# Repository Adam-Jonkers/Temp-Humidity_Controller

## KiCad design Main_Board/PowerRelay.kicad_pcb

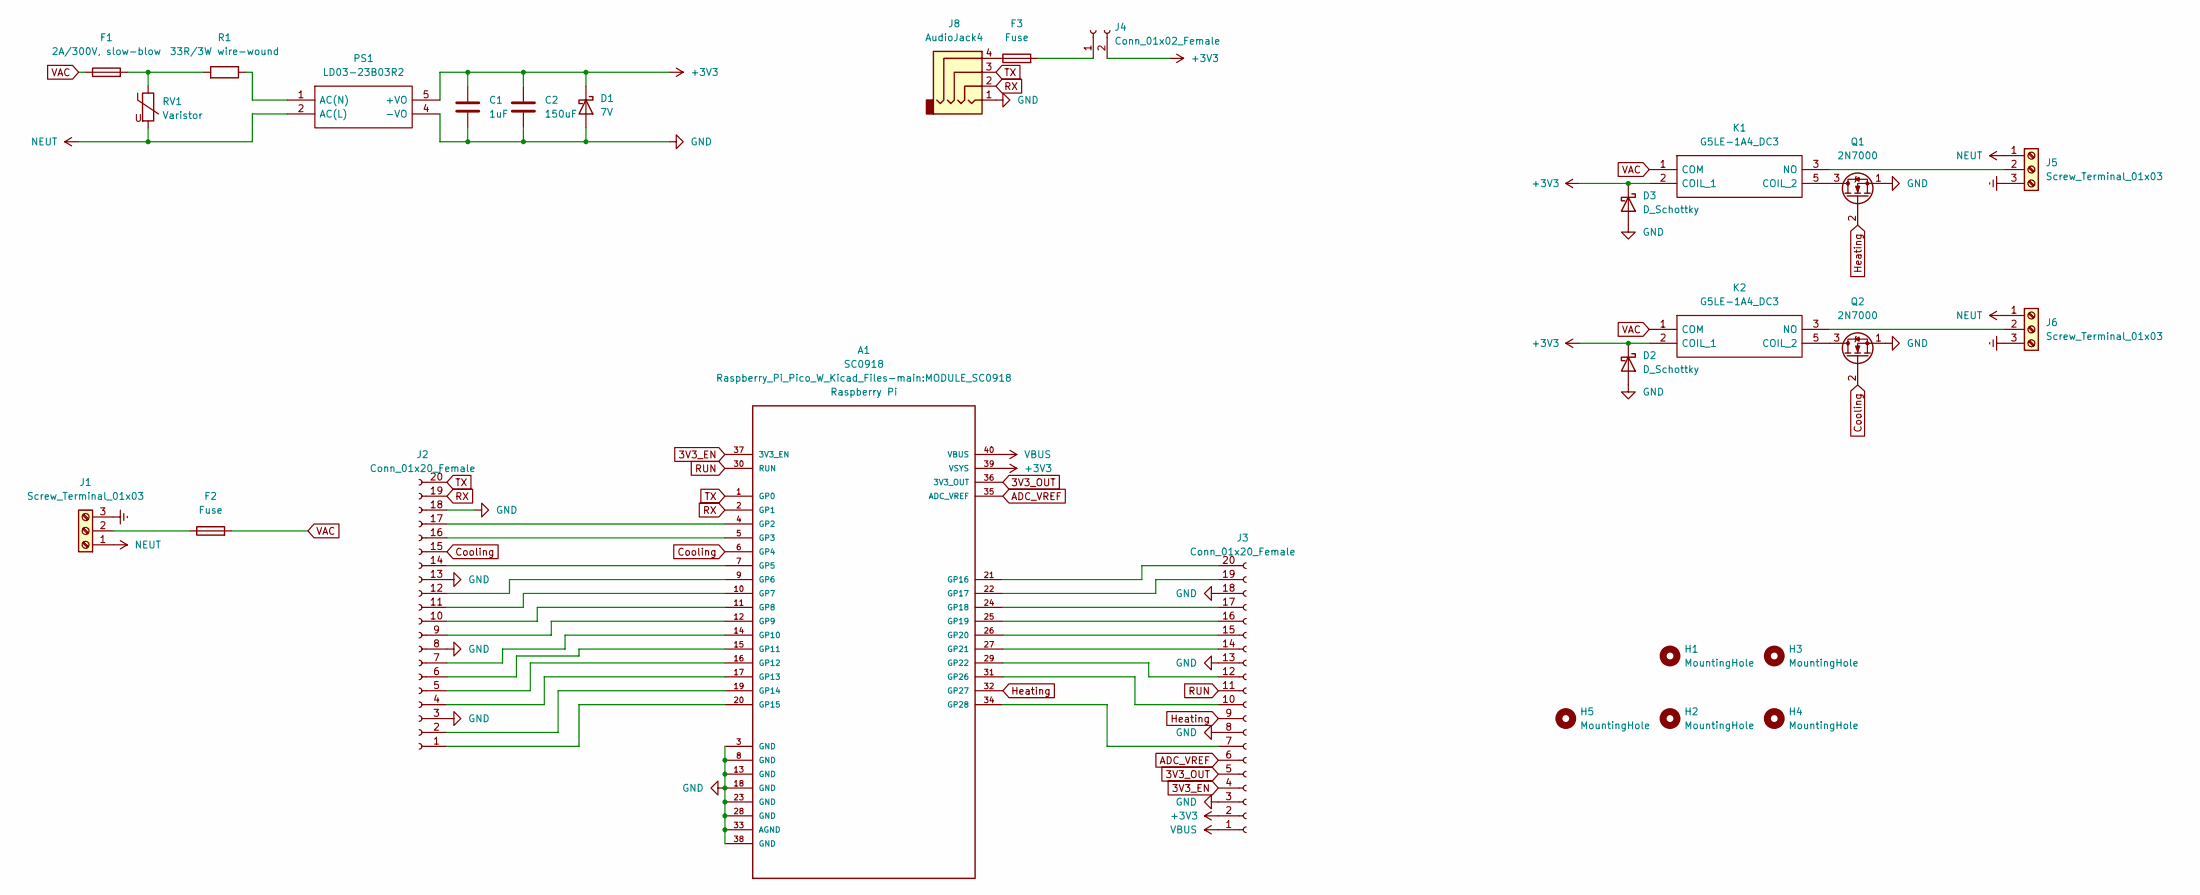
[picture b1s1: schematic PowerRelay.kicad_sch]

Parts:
A1: SC0918; MODULE_SC0918; PARTREV 1.6
C1: 1uF; C_Disc_D5.0mm_W2.5mm_P2.50mm
C2: 150uF; CP_Radial_D6.3mm_P2.50mm
D1: 7V; SA7.0A-E3_54
D2, D3: D_Schottky; DIOAD1300W80L670D310
F1: 2A/300V, slow-blow; 38312000000
F2: Fuse; 696105003002
F3: Fuse; 39105000000
H1, H2, H3, H4, H5: MountingHole; MountingHole_3mm
J1, J5, J6: Screw_Terminal_01x03; 1760520000
J2, J3: Conn_01x20_Female; PinHeader_1x20_P2.54mm_Vertical
J4: Conn_01x02_Female; PinHeader_1x02_P2.54mm_Vertical
J8: AudioJack4; 54-00174_JACK
K1, K2: G5LE-1A4_DC3; G5LE1A4DC3; Manufacturer_Part_Number G5LE-1A4 DC3; Mouser Part Number 653-G5LE-1A4DC3
PS1: LD03-23B03R2; LD0323B03R2; Manufacturer_Part_Number LD03-23B03R2
Q1, Q2: 2N7000; BS270
R1: 33R/3W wire-wound; AC03000003309JACCS
RV1: Varistor; B72214P2351K101

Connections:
3V3_EN: A1.37 (3V3_EN), J3.4
3V3_OUT: A1.36 (3V3_OUT), J3.5
+3V3: A1.39 (VSYS), C1.1, C2.1, D1.1 (K), D2.1 (K), D3.1 (K), J3.2, J4.2, K1.2 (COIL_1), K2.2 (COIL_1), PS1.5 (+VO)
ADC_VREF: A1.35 (ADC_VREF), J3.6
Cooling: A1.6 (GP4), J2.15, Q2.2 (G)
Earth: J1.3, J5.3, J6.3
GND: A1.3 (GND), A1.8 (GND), A1.13 (GND), A1.18 (GND), A1.23 (GND), A1.28 (GND), A1.33 (AGND), A1.38 (GND), C1.2, C2.2, D1.2 (A), D2.2 (A), D3.2 (A), J2.3, J2.8, J2.13, J2.18, J3.3, J3.8, J3.13, J3.18, J8.1, PS1.4 (-VO), Q1.1 (S), Q2.1 (S)
Heating: A1.32 (GP27), J3.9, Q1.2 (G)
NEUT: J1.1, J5.1, J6.1, PS1.2 (AC(L)), RV1.2
unnamed: A1.4 (GP2), J2.17
unnamed: A1.5 (GP3), J2.16
unnamed: A1.7 (GP5), J2.14
unnamed: A1.9 (GP6), J2.12
unnamed: A1.10 (GP7), J2.11
unnamed: A1.11 (GP8), J2.10
unnamed: A1.12 (GP9), J2.9
unnamed: A1.14 (GP10), J2.7
unnamed: A1.15 (GP11), J2.6
unnamed: A1.16 (GP12), J2.5
unnamed: A1.17 (GP13), J2.4
unnamed: A1.19 (GP14), J2.2
unnamed: A1.20 (GP15), J2.1
unnamed: A1.21 (GP16), J3.20
unnamed: A1.22 (GP17), J3.19
unnamed: A1.24 (GP18), J3.17
unnamed: A1.25 (GP19), J3.16
unnamed: A1.26 (GP20), J3.15
unnamed: A1.27 (GP21), J3.14
unnamed: A1.29 (GP22), J3.12
unnamed: A1.31 (GP26), J3.10
unnamed: A1.34 (GP28), J3.7
unnamed: F1.2, R1.2, RV1.1
unnamed: F3.1, J8.4
unnamed: F2.1, J1.2
unnamed: F3.2, J4.1
unnamed: J5.2, K1.3 (NO)
unnamed: J6.2, K2.3 (NO)
unnamed: K1.5 (COIL_2), Q1.3 (D)
unnamed: K2.5 (COIL_2), Q2.3 (D)
unnamed: PS1.1 (AC(N)), R1.1
RUN: A1.30 (RUN), J3.11
RX: A1.2 (GP1), J2.19, J8.2
TX: A1.1 (GP0), J2.20, J8.3
VAC: F1.1, F2.2, K1.1 (COM), K2.1 (COM)
VBUS: A1.40 (VBUS), J3.1

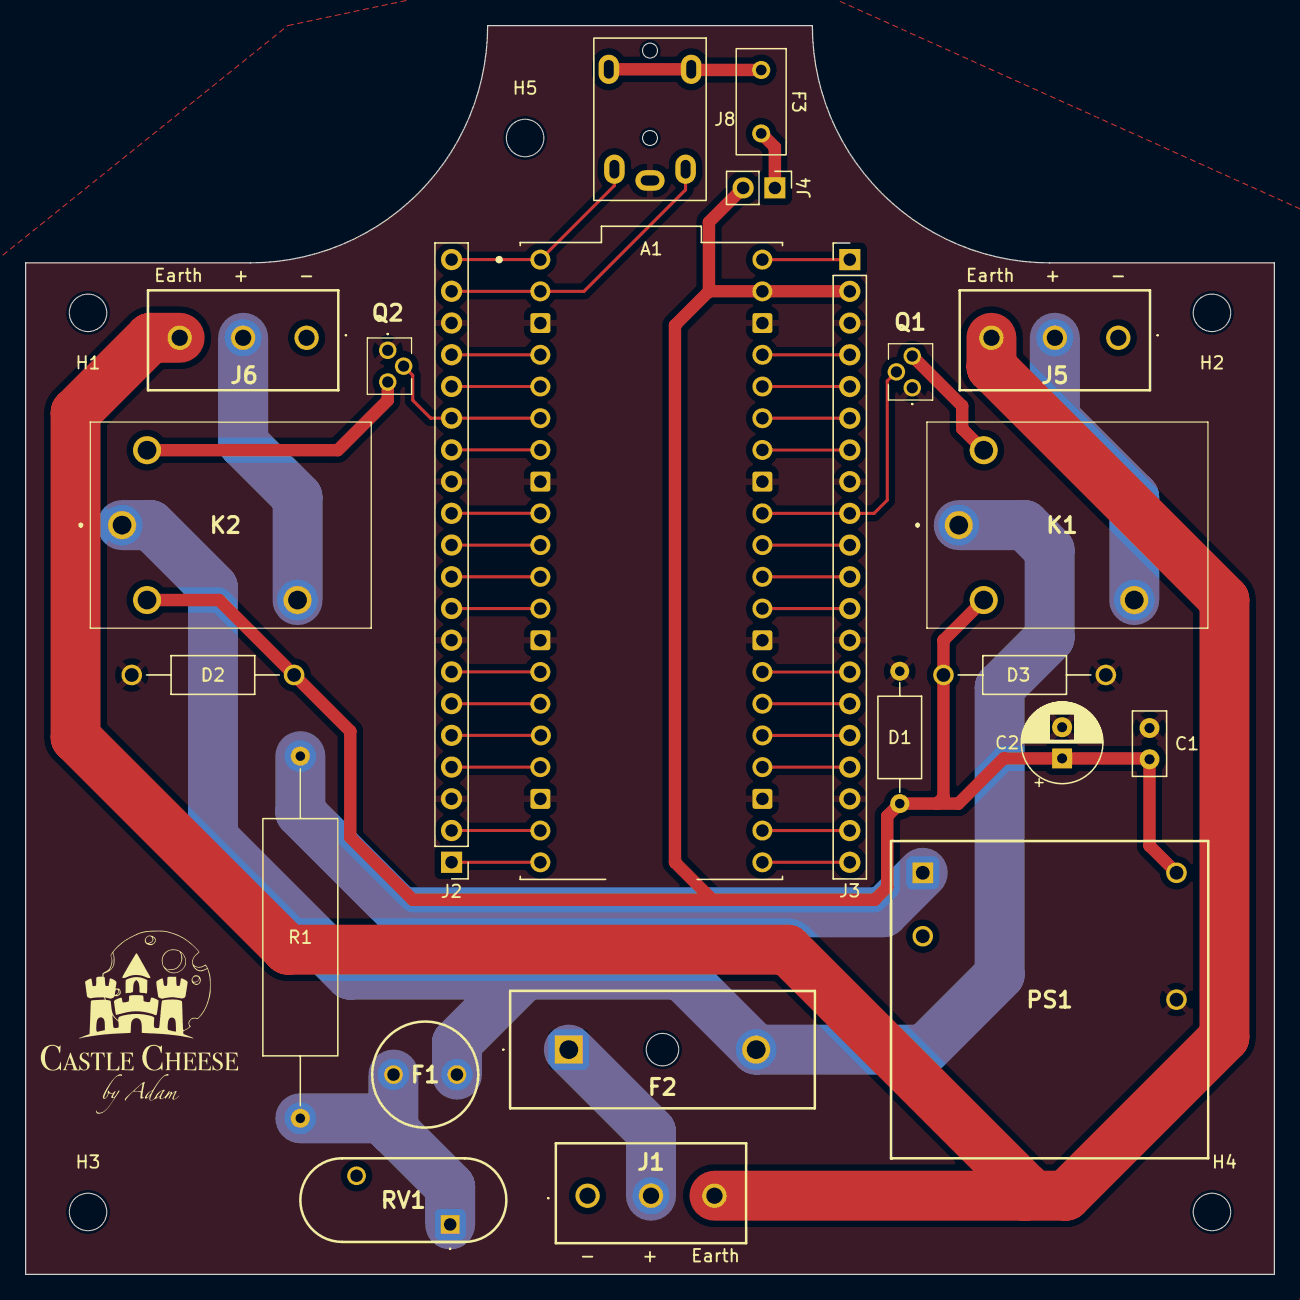
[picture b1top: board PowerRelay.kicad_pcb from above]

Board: 2 copper layers, 100.0 x 100.0 mm, 28 parts (0 on the bottom side), 45 nets.

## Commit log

2023-04-04 add ignore
2023-04-04 add current version of pcb design
2023-04-04 add power label for ac power connectors to silkscreen
2023-04-04 added intruction for later
2023-04-07 add aux port for inter board comunication
2023-04-07 add logo to board
2023-04-07 slight edit to move man on back inbetween pico headers
2023-04-07 make space to shift power headers back
2023-04-07 add cutout for plugs to sit
2023-04-07 re organize files to make it easier to have multiple boards
2023-04-09 change footprint for barrel connector
2023-04-11 multiple changes and convert to ki cad 7
2023-04-21 add initial files for casing
